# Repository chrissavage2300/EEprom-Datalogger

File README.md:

The purpose of this project is to take in readings from various sensors (Light and Temperature) and store them in a EEprom. I re-started this project because I wanted to log temperature and the amount of light in a particular area for a garden. I wanted it to be small and not be a full fledged datalogger with a transmitter.

Features:
* Capacitor Backup that will last at the very least 12 hours (During the night)
* Solar charging during the day
* Integrated ORing power circuit so it will charge the capacitor and run the supporting circuitry
* According to my calculations, for a whole year of 1 reading per hour every day I will need about 8kb of memory per sensor. ADC readings iwll be 8 bits each. In practice there's no need for a 10 bit ADC.
* 32kHz Clock run from Timer 1 for accurate timing
* Why Supercapacitor? Temperature range pretty much. Lithium's only go down to 0C and often times temperatures dip below that. Supercapacitors have a range of -40C to 60C which covers the range of outdoor temperatures. 
* Ive integrated a set of UART commands to feedback the status of the micro. It will always take data, there is no stop.
* Upgraded the caps from 3F to 2x6F for a total of 12F. This should last about 27 hours at 370uA consumption. I never could figure out where that is all going, but its not the micro. It only takes 2-3 minutes to charge in full sun though. So even if its cloudy or the sun panel isnt efficient enough, it only needs a few minutes to charge fully. 
* Note: When sending UART commands a "1" has to come before it, so "1a" to read the EEprom. This is by design to wake up the micro so it can recieve stuff properly.
* The Micro Keeps track of the current EEprom address. One issue is that if power ever does get low enough, it will lose the current EEprom address and therefore return to 0 and then all data will be lost. I could have dumped in the EEprom address into the micro's own EEprom and store it if power gets low, but I chose not to.

Commands are as follows:
* "1a" = Read EEprom
* "1E" = Erase EEprom
* "1q" = Status, spits out Seconds,Minutes,MaxAddress,Temp,Solar in that order
* "1t" = current time in MM:SS. Does not track hours passed. 
* "1m" = Used Memory Locations. Shows how much memory has been written to. Currently, two bytes get written into the EEprom

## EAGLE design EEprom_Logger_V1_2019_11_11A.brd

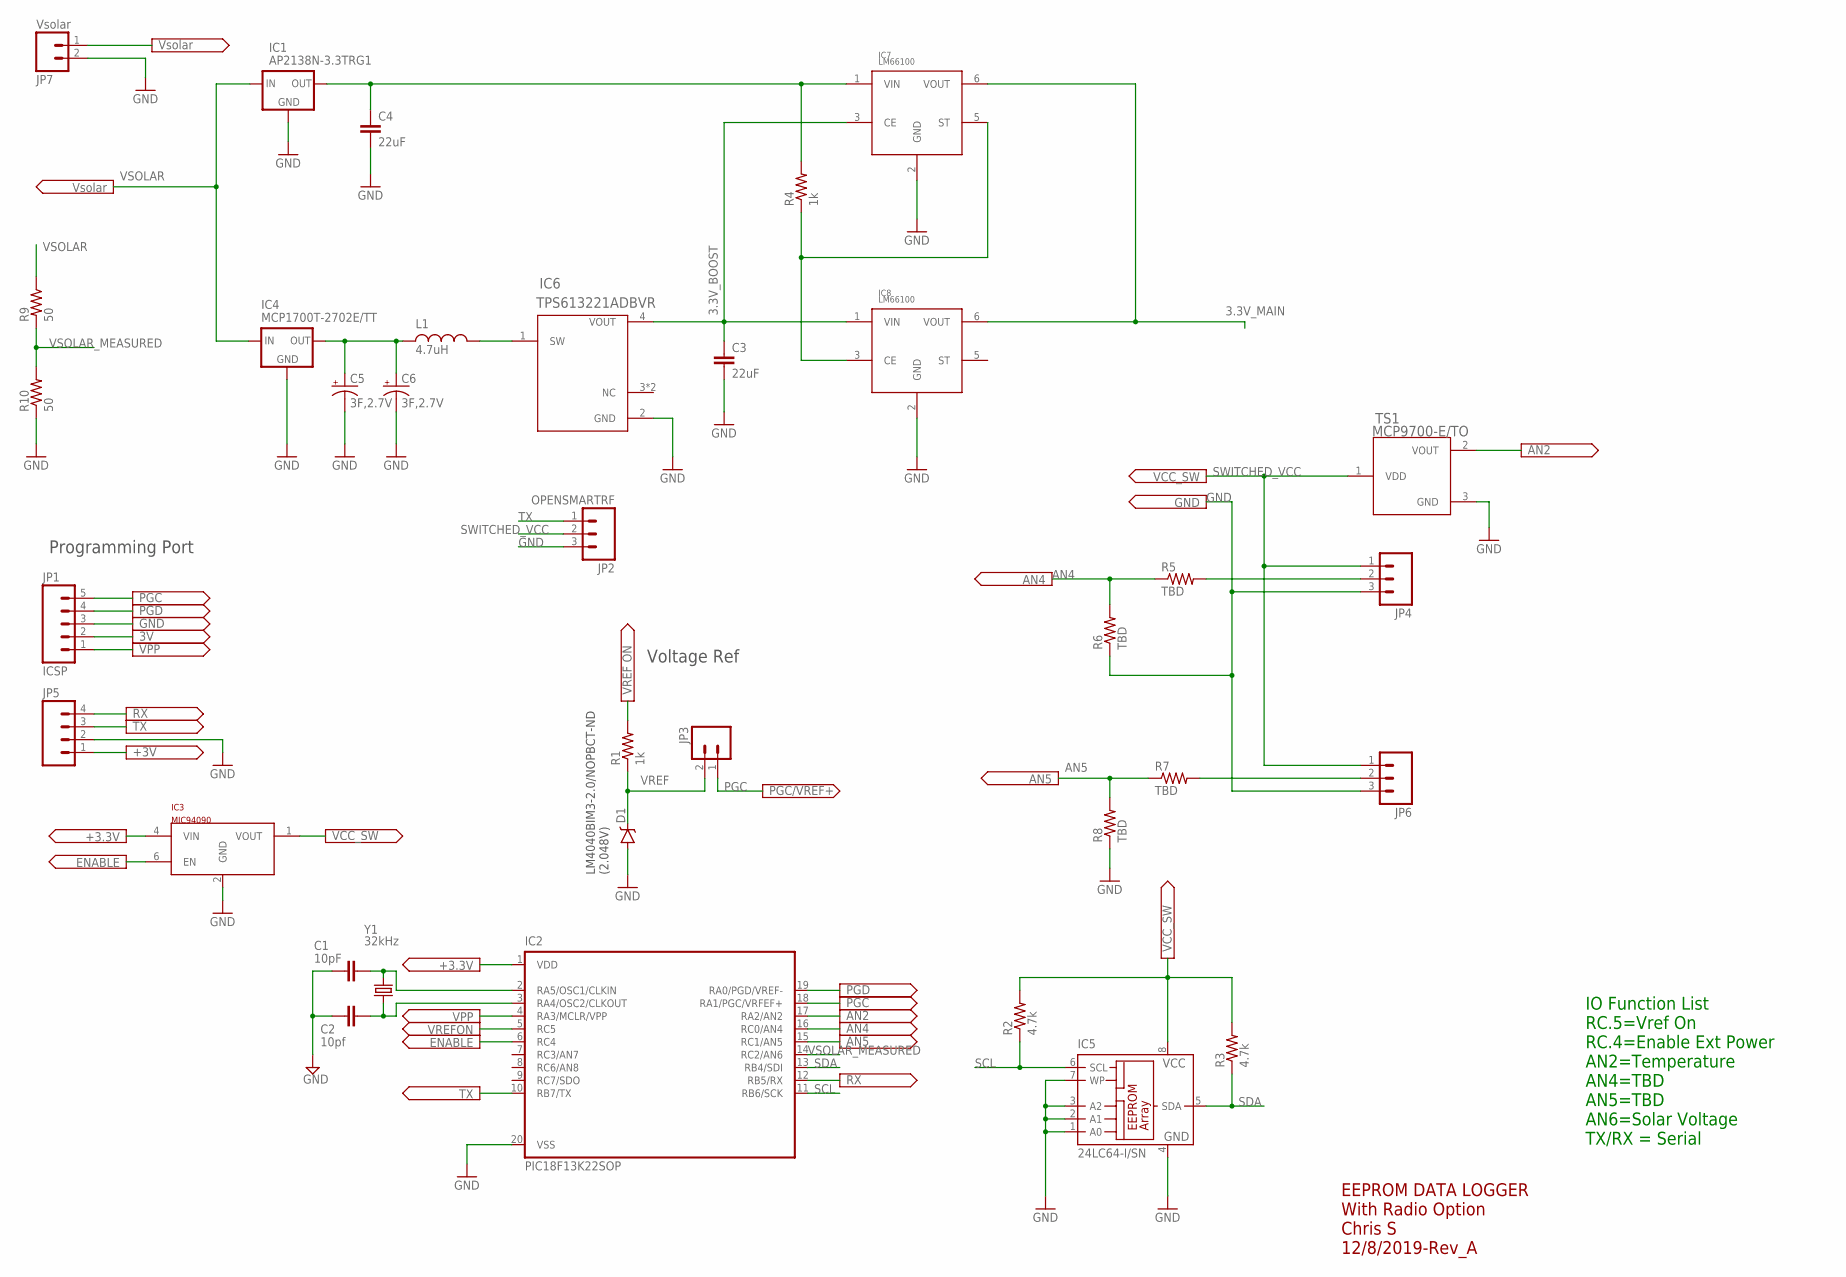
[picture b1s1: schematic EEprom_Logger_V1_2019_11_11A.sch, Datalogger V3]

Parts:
C1: 10pF; 1206
C2: 10pf; 1206
C3, C4: 22uF; 1206
C5, C6: 3F,2.7V; E3,5-8
D1: V-REFERENCESMD; SOT23-3
IC1: AP2138N-3.3TRG1; SOT23
IC2: PIC18F13K22SOP; SOP20W
IC3: MIC94090; SC-70
IC4: MCP1700T-2702E/TT; SOT23
IC5: 24LC64-I/SN; SO-08
IC6: TPS613221ADBVR; DBV5-L
IC7, IC8: LM66100; SC70-6
JP1: ICSP; 1X05
JP2: OPENSMARTRF; 1X03_LONGPADS@1
JP3: M02LOCK; 1X02_LOCK
JP4, JP6: 455-1750-1-ND; 1X03
JP5: M04PTH; 1X04
JP7: Vsolar; MOLEX-1X2_LOCK@1
L1: 4.7uH; 1210
R1, R4: 1k; 1206
R2, R3: 4.7k; 1206
R5, R6, R7, R8: TBD; 1206
R9, R10: 50; 1206
TS1: MCP9700-E/TO; TO-92-AMMO
Y1: 32kHz; TC26V

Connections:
3.3V_BOOST: C3.2, IC6.4 (VOUT), IC7.3 (CE), IC8.1 (VIN)
3.3V_MAIN: IC2.1 (VDD), IC3.4 (VIN), IC7.6 (VOUT), IC8.6 (VOUT), JP1.2, JP5.1
AN2: IC2.17 (RA2/AN2), TS1.2 (VOUT)
AN4: IC2.16 (RC0/AN4), R5.1, R6.2
AN5: IC2.15 (RC1/AN5), R7.1, R8.2
ENABLE: IC2.6 (RC4), IC3.6 (EN)
GND: C1.2, C2.2, C3.1, C4.1, C5.-, C6.-, D1.2 (A), IC1.1 (GND), IC2.20 (VSS), IC3.2 (GND), IC4.1 (GND), IC5.1 (A0), IC5.2 (A1), IC5.3 (A2), IC5.4 (GND), IC5.7 (WP), IC6.2 (GND), IC7.2 (GND), IC8.2 (GND), JP1.3, JP2.3, JP4.3, JP5.2, JP6.3, JP7.2, R6.1, R8.1, R10.1, TS1.3 (GND)
unnamed: C1.1, IC2.2 (RA5/OSC1/CLKIN), Y1.2
unnamed: C2.1, IC2.3 (RA4/OSC2/CLKOUT), Y1.1
unnamed: C4.2, IC1.2 (OUT), IC7.1 (VIN), R4.2
unnamed: C5.+, C6.+, IC4.2 (OUT), L1.1
unnamed: IC7.5 (ST), IC8.3 (CE), R4.1
unnamed: JP4.2, R5.2
unnamed: IC6.1 (SW), L1.2
unnamed: JP6.2, R7.2
PGC: IC2.18 (RA1/PGC/VRFEF+), JP1.5, JP3.1
PGD: IC2.19 (RA0/PGD/VREF-), JP1.4
RX: IC2.12 (RB5/RX), JP5.4
SCL: IC2.11 (RB6/SCK), IC5.6 (SCL), R2.1
SDA: IC2.13 (RB4/SDI), IC5.5 (SDA), R3.1
SWITCHED_VCC: IC3.1 (VOUT), IC5.8 (VCC), JP2.2, JP4.1, JP6.1, R2.2, R3.2, TS1.1 (VDD)
TX: IC2.10 (RB7/TX), JP2.1, JP5.3
VPP: IC2.4 (RA3/MCLR/VPP), JP1.1
VREF: D1.1 (C), JP3.2, R1.1
VREFON: IC2.5 (RC5), R1.2
VSOLAR: IC1.3 (IN), IC4.3 (IN), JP7.1, R9.1
VSOLAR_MEASURED: IC2.14 (RC2/AN6), R9.2, R10.2

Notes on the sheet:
LM4040BIM3-2.0/NOPBCT-ND (2.048V)
Voltage Ref
Programming Port
EEPROM DATA LOGGER With Radio Option Chris S 12/8/2019-Rev_A
IO Function List RC.5=Vref On RC.4=Enable Ext Power AN2=Temperature AN4=TBD AN5=TBD AN6=Solar Voltage TX/RX = Serial

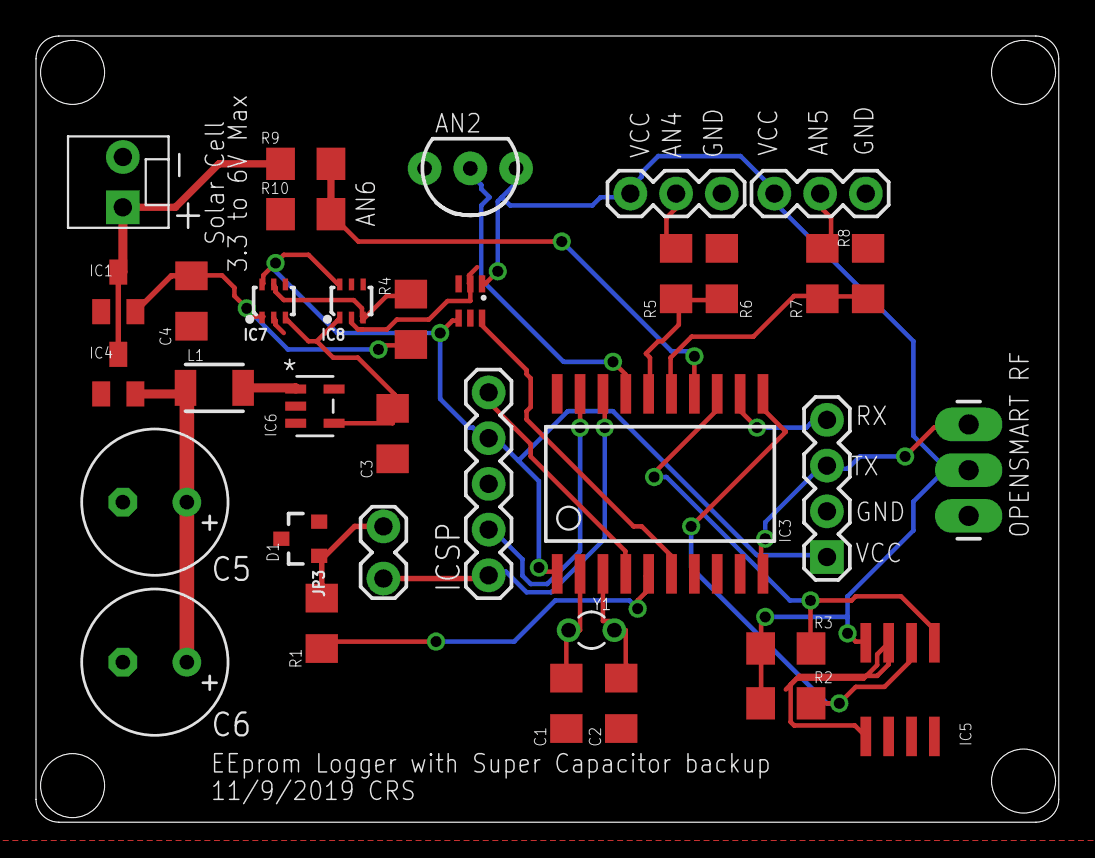
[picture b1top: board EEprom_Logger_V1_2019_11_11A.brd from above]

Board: 2 copper layers, 56.8 x 43.7 mm, 35 parts (0 on the bottom side), 27 nets.

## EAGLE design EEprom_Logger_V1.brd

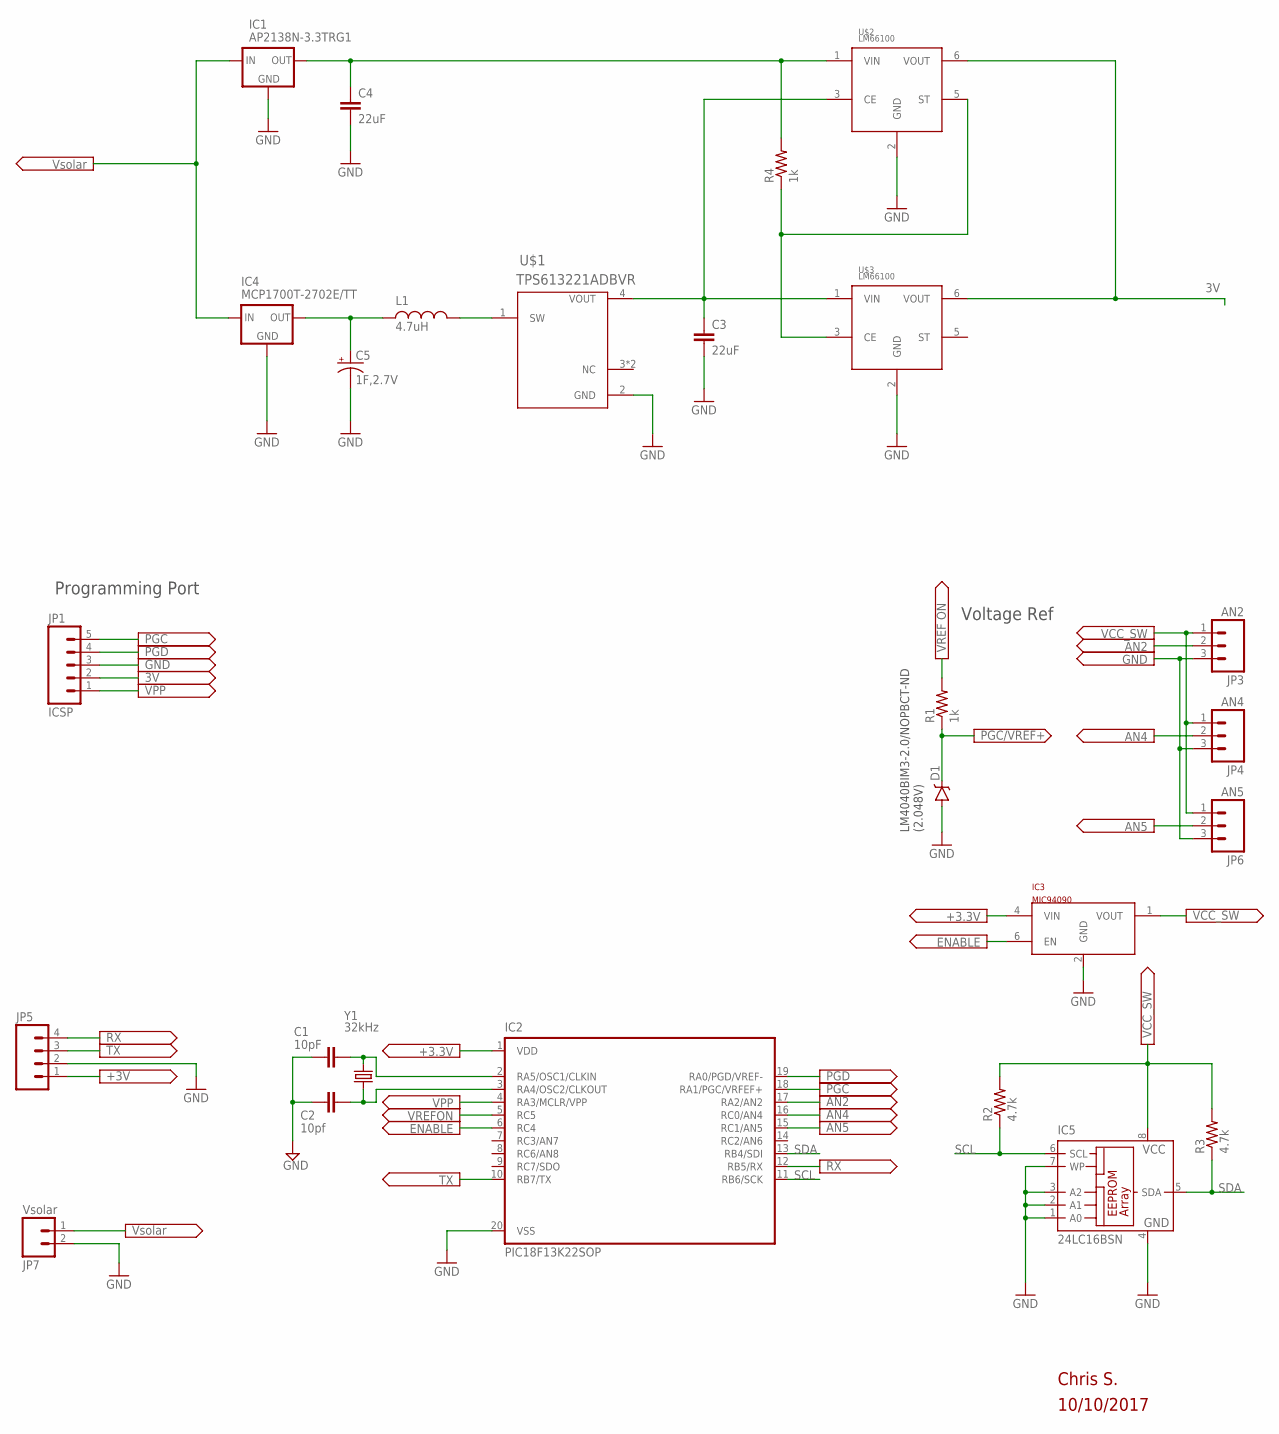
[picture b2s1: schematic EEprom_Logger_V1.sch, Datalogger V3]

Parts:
C1: 10pF; 1206
C2: 10pf; 1206
C3, C4: 22uF; 1206
C5: 1F,2.7V; E3,5-8
D1: V-REFERENCESMD; SOT23-3
IC1: AP2138N-3.3TRG1; SOT23
IC2: PIC18F13K22SOP; SOP20W
IC3: MIC94090; SC-70
IC4: MCP1700T-2702E/TT; SOT23
IC5: 24LC16BSN; SO-08
JP1: ICSP; 1X05
JP3: AN2; JST-3-PTH
JP4: AN4; JST-3-PTH
JP5: M04PTH; 1X04
JP6: AN5; JST-3-PTH
JP7: Vsolar; JST-2-PTH
L1: 4.7uH; 1210
R1, R4: 1k; 1206
R2, R3: 4.7k; 1206
U$1: TPS613221ADBVR; DBV5-L
U$2, U$3: LM66100; SC70-6
Y1: 32kHz; TC26V

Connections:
3V: IC2.1 (VDD), IC3.4 (VIN), JP1.2, JP5.1, U$2.6 (VOUT), U$3.6 (VOUT)
AN2: IC2.17 (RA2/AN2), JP3.2
AN4: IC2.16 (RC0/AN4), JP4.2
AN5: IC2.15 (RC1/AN5), JP6.2
ENABLE: IC2.6 (RC4), IC3.6 (EN)
GND: C1.2, C2.2, C3.1, C4.1, C5.-, D1.2 (A), IC1.1 (GND), IC2.20 (VSS), IC3.2 (GND), IC4.1 (GND), IC5.1 (A0), IC5.2 (A1), IC5.3 (A2), IC5.4 (GND), IC5.7 (WP), JP1.3, JP3.3, JP4.3, JP5.2, JP6.3, JP7.2, U$1.2 (GND), U$2.2 (GND), U$3.2 (GND)
unnamed: C1.1, IC2.2 (RA5/OSC1/CLKIN), Y1.2
unnamed: C2.1, IC2.3 (RA4/OSC2/CLKOUT), Y1.1
unnamed: C4.2, IC1.2 (OUT), R4.2, U$2.1 (VIN)
unnamed: C5.+, IC4.2 (OUT), L1.1
unnamed: IC1.3 (IN), IC4.3 (IN)
unnamed: R4.1, U$2.5 (ST), U$3.3 (CE)
unnamed: C3.2, U$1.4 (VOUT), U$2.3 (CE), U$3.1 (VIN)
unnamed: L1.2, U$1.1 (SW)
PGC: D1.1 (C), IC2.18 (RA1/PGC/VRFEF+), JP1.5, R1.1
PGD: IC2.19 (RA0/PGD/VREF-), JP1.4
RX: IC2.12 (RB5/RX), JP5.4
SCL: IC2.11 (RB6/SCK), IC5.6 (SCL), R2.1
SDA: IC2.13 (RB4/SDI), IC5.5 (SDA), R3.1
SWITCHED_VCC: IC3.1 (VOUT), IC5.8 (VCC), JP3.1, JP4.1, JP6.1, R2.2, R3.2
TX: IC2.10 (RB7/TX), JP5.3
VPP: IC2.4 (RA3/MCLR/VPP), JP1.1
VREFON: IC2.5 (RC5), R1.2
VSOLAR: JP7.1

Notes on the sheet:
LM4040BIM3-2.0/NOPBCT-ND (2.048V)
Voltage Ref
Chris S.
10/10/2017
Programming Port

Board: 2 copper layers, 26 parts (0 on the bottom side), 23 nets, no tracks yet.

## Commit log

2019-10-03 Create Code
2019-10-11 Rename README.md to Preliminary Parts list.md
2019-10-11 Rename about.md to README.md
2020-02-17 Add files via upload
    Current code takes data at 1 minute intervals. Code also stops the datalogging once you erase the EEprom. Bug or Feature?

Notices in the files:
parts and their libraries:
SparkFun-Connectors: Licensing: Creative Commons ShareAlike 4.0 International - https://creativecommons.org/licenses/by-sa/4.0
